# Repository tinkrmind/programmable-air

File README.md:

## NOTE: Development of Programmable-Air has moved to [Programmable-Air Org repo](https://github.com/programmable-air). This repo is maintained for the sake of completeness but is no longer actively maintained. Please use [Programmable-Air Org repo](https://github.com/programmable-air) for code and reference material.

## Buzz

* [Hackaday mention!](https://hackaday.com/2018/05/24/programmable-air-makes-robotics-a-breeze/)
* [Hackster mention!!](https://blog.hackster.io/programmable-air-is-an-arduino-based-air-pump-for-your-soft-robotics-projects-9945c6ed96aa)
* [Maker Faire](https://makerfaire.com/maker/entry/67747/)

## Elevator Pitch

### [Slideshow](https://docs.google.com/presentation/d/1pUnGk4v_wuCpisjBpNWZSJUyDwAFb4v1xceV4rX-Uv4/edit?usp=sharing)

I started out making in earnest at IISc where I saw researchers being exploited by hardware manufacturers. Sub-par equipment is often lauded as the best solution only because it's the only solution. As a result I worked directly with researchers making equipment for measuring elephant height, insect wing- beat frequency, underwater gates for fishes.. I see the same issue with soft robotics today.

The field of inflatable robotics is still in its infancy. So there are a lot of low hanging fruit up for grabs. As such, the more people involved in active experimentation, the faster the field will mature.

Working with inflatables involves a lot of prototyping as a part of the design process. To do any repeatable experiments with inflatables, a controllable air source is required.

I feel there isn't any affordable and easy to use programmable air source available for makers right now. This is a barrier to entry. Programmable Air is my attempt to create a bottom of the line air source that is cheaper and easier to use than anything available right now. The market is strapped for cash makers and schools.

### What can you use it for?

#### Vacuum

###### [* Electronic component pick and place.](https://vimeo.com/268358924)

###### [* Universal vacuum based gripper.](https://vimeo.com/268358891)

#### Inflatable

###### [* Crazy soft robots]()

###### [* Balloons!](https://vimeo.com/268358970)

##### [* Small air brush?](https://vimeo.com/268163619)

Doesn't really work. You can get it to work if the air brush is pointing down and mars is on retrograde :P Check out the failed video below. Maybe it'll give you an idea for how you can improve on it.

 Most airbrushes seem to require around 10L/min air flow rate and the current pump can only deliver 1-2L/min. This small one just barely works with the pumps.

#### Pressure sensor

##### [* Large Impact Sensors]((https://vimeo.com/268358944)

Any closed inflated object can be used as an impact sensor when connected to the air pressure sensor e.g. a large flexible tube with one end closed off and another connected to the pressure sensor. When the tube is pressed a pressure spike is recorded by the sensor. This tube can be looped around a bumper car for example to act as an impact sensor.

##### [Exhalation](https://vimeo.com/268359027)

Controlling the air pressure inside a closed chamber allows a soft robot place in the chamber to behave as if it is being controlled without any tubes connected to  it. This facilitates easy prototyping and some funky art pieces. Inspired from [Exhalation](http://escapepod.org/2009/04/10/ep194-exhalation/) by Ted Chiang.

### What's wrong with the current solutions?

#### Pneuduino: [link](http://pneuduino.org/)

Not available for purchase. Potentially fallen out of development(last commit on github was about two years and the primary engineer has graduated out of the program.)

#### Fluidic control system: [link](https://softroboticstoolkit.com/book/control-board)

Truly designed by researchers for reserchers. Ugly. Complicated to setup. Needlessly expensive. [BOM](https://softroboticstoolkit.com/book/controlboard-bom)

Methods of potentially reducing cost:

- __Cheaper pump__: The [current pump](http://ph.parker.com/us/12051/en/btc-iis-and-ttc-iis-miniature-diaphragm-pump) at ~288$ is overpriced if not necessarily overspec'ed. I'm confident a replacement would be available for one tenth the cost.
- __Cheaper valves__: High switching rate is not necessary for most applications. The current valves cost ~175$. An acceptable replacement would be [this](https://www.elecrow.com/dc12v-four-way-valve-independent-control-solenoid-valve.html) at ~10$. Since pressure is controlled by PWM of the valves, this may lead to some issues if these actuators can't be driven fast enough. Some slack can be made up for by adding a "capacitor" after the valve. But, if the actuation time is of the order of hundreds of milliseconds, I may need a different approach. One such approach can be servo driven drip knobs. Another approach could be a linear actuator driving a plate covering a slit
- __Get rid of the power boards__: There's no need for a 24V in which then gets converted to 12V and 5V on board. It adds bulk and points of failure. Separate 12V and 5V wall warts will be much more reliable and cheaper. Cost saving ~20$
- Get rid of mosfets: A ULN2803 would be just as well suited to the task at a fraction of the price. It would also be much more reliable against electrostatic shock.
- __Cheaper air pressure sensors__: The same vendor makes [pressure sensors](https://www.digikey.com/product-detail/en/honeywell-sensing-and-productivity-solutions/NBPLANN100PAUNV/480-5540-ND/3475899) at a forth the price, which only need minimal external circuit to become nearly as accurate. This would add complexity to the first design of the build but bulm manufacture would benefit from the cost saving.
- __Cheaper arduino alternative__: An arduino mega is overkill for this. Any atmega324 based boards is sufficient

The __weakest link__ in this setup however is the __mess of jumper cable__ connections. There is no justifiable reason for a beginners kit to be this complicated to setup especially when the cost can be reduced simultaneously by making the setup into a PCB.

### Let's start making!

The common pressures are of the range -0.5 atm to 2.5 atm. Ideally we'd want to work in this entire range. Ideally, the pressure profile would be editable over a web interface, without any software/driver installation.

#### Learning basic fluid mechanics and the lingo of the field

Choosing a pressure sensor is tough! There's far too many choices and every datasheet seems to have come from a different universe. Who uses hectoPascals?! Here's some bare minimum info you need before searching for sensors:

-  [Difference between absolute, guage and differential sensors](https://www.first-sensor.com/en/products/pressure-sensors/pressure-sensors-and-transmitters/pressure-types.html)
- [DigiKey sensor guide](https://www.digikey.com/en/resources/sensors/pressure-sensors)
- [Basic of fluid physics](http://www.pneumaticsonline.com/BasicTraining/default.htm)

### Minimum Viable Product

The problem to be solved here is reducing cost without compromising on function. To reduce cost, component specifications have to be matched. The max pressure deliverable by the motor should be close to the pressure limits of the sensor. Given dozens of choices for sensors, motors and valves this is not an easy exercise. Especially, when we're aiming at a moving target specification.

To make life easier, I decided to go for following minimum specifications
* -0.5 atm to +0.5 atm pressure range,
* two air channels
* 2 Liter/min flow rate
* Able to inflate and deflate a 6 inch balloon in under 30 seconds
* Five minute setup time
* Cross platform compatability(Win, Mac, Linux)
* Cost under 100$/set for a production run of 5 sets

### Evaluating off the shelf components

|Item|Inner Dia Eqv|Voltage|Link|Cost per item|Remarks|
|---|---|---|---|---|---|
|Similk aquarium +pump|3/16"|6V|[Amazon](https://www.amazon.com/gp/product/B071FC3C9L/ref=ox_sc_act_title_3?smid=A30FBXYHCPC2G9&psc=1)|4$||
|DIminus aquarium +pump|3/16"|6V|[Amazon](https://www.amazon.com/gp/product/B071GNFHGX/ref=ox_sc_act_title_1?smid=A1KXN55BWHRB5I&psc=1)|4.5$||
|Medical -pump|3/16"|12V|[Amazon](https://www.amazon.com/gp/product/B01MR3JZZF/ref=ox_sc_act_title_4?smid=A3BG62S1F23IH5&psc=1)|9$||
|Square Medical -pump|3/16"|12V|[Amazon](https://www.amazon.com/gp/product/B071GNFHGX/ref=ox_sc_act_title_1?smid=A1KXN55BWHRB5I&psc=1)|11$|Low stock|
|Ohaha tube connectors|3/16"|N/A|[Amazon](https://www.amazon.com/gp/product/B06XHX1KWL/ref=ox_sc_act_title_1?smid=A1665Y00LA4JOM&psc=1)|8$/set of hundred connectors||
|Aquarium -pump|3/16"|5-12V|[Amazon](https://www.amazon.com/Electric-Self-Priming-Suction-Aluminum-Diaphragm/dp/B0786CX98Q/ref=pd_day0_199_5?_encoding=UTF8&pd_rd_i=B0786CX98Q&pd_rd_r=Y0RNFT06BCCAAB1NR6KJ&pd_rd_w=0L70O&pd_rd_wg=gJkuo&psc=1&refRID=Y0RNFT06BCCAAB1NR6KJ)|10$||
|Pink-day -pump|3/16"|12V|[Amazon](https://www.amazon.com/Pink-day-Electric-Motor-Vacuum-Booster/dp/B076VLXHYB/ref=sr_1_9?ie=UTF8&qid=1523048670&sr=8-9&keywords=vacuum+pump+mini)|5$|Slow shipping|
|Woolf -pump|3/16"|3-6V|[Amazon](https://www.amazon.com/3V-6V-Motor-Vacuum-Aquarium-Oxygen/dp/B074PPV6QH/ref=sr_1_15?ie=UTF8&qid=1523048670&sr=8-15&keywords=vacuum+pump+mini)|4$|Slow Shipping|
|Valve 2way|3mm|5V|[Amazon](https://www.amazon.com/gp/product/B00JR3ZQSC/ref=od_aui_detailpages00?ie=UTF8&psc=1)|7.5$||
|Omron +-pressure sensor|3mm|Wheatstone|[DigiKey](https://www.digikey.com/product-detail/en/omron-electronics-inc-emc-div/2SMPP03/Z3639-ND/3671590)|8$|Needs HX711+LM10CN or [INA125](https://learn.adafruit.com/smart-cocktail-shaker/hardware) to work with arduino|
|3 way valve|3/16"|12V|[Elecrow](https://www.elecrow.com/electric-2-position-3-way-12v-micro-solenoid-valve-for-gas.html)|2.5$||
|2 way valve|3/16"|12V|[MPJA](http://www.mpja.com/Solenoid-Valve-Normally-Closed-12VDC-Used/productinfo/33957+HD), [Manufacturer](https://translate.google.com/translate?hl=en&sl=zh-CN&u=http://www.conjoin.com.cn/products.php%3Fl%3D5&prev=search), [SkyCraft](https://www.skycraftsurplus.com/12vdcpneumaticsolenoidvalve-1.aspx)|2.95$|Reused components. Not scalable.|
|2 way valve |3/16"|12V|[Alibaba](https://jmakervalve.en.alibaba.com/product/60692195756-805059697/JMKV20_BB12A1_2_way_12v_dc_water_solenoid_valve_for_high_end_medical_equipment.html?spm=a2700.icbuShop.prewdfa4cf.86.41256ab8Fp0fQF)|

### Choice of pressure sensor: [2SMPP03](https://www.digikey.com/product-detail/en/omron-electronics-inc-emc-div/2SMPP03/Z3639-ND/3671590)

It's easy for the pressure sensor to be the most expensive piece in the kit. Since one pressure sensor is required for every pneumatic channel, the cost scales linearly with number of channels. Pressure sensors that work in <-0.5 atm to >+0.5 atm range are relatively expensive since few large industries demand such a sensor. The cheapest such sensor I could find is [2SMPP03](https://www.digikey.com/product-detail/en/omron-electronics-inc-emc-div/2SMPP03/Z3639-ND/3671590) by Omron electronics. It is priced at <7$/per unit for 5 units and while it needs additional circuitry to work, the effort is well worth it. The cheapest sensor that works standalone is at least 30$/per unit at 5 units. So I have designed the rest of the system around this sensor.

### v0.1 PCB design

Used Aiyima pumps and an Arduino Nano on master board. The slave board has pressure sensor and three two way valves. Upto four slave boards can attach to a single master board, as shown in mock-up below.

#### Learnings from design and manufacture:

The rated current for DC motors can differ highly from the actual current consumed. While the motors are rated at 350mA, a 0.8A transistor blew up while trying to supply enough current to it. This could be because of high stall/startup current. v0.11 will have TIP120 or FET rated to at least 2A. The valves are rated at 0.11A so, using a 2222 transistor seems like a safe bet because they can handle peak currents of up to 0.8A(a 7x margin). Because these are much cheaper than TIP120, it makes sense to use them.

As a result of design oversight, the was no 5V power connection from master to slave board. While 12V input to slave board can be converted to a clean 5V with a relatively cheap regulator, v0.11 will have power connections for 5V as well. Added filter capacitors to all power rails in v0.11.

I manufactured the PCBs in an OtherMill CNC. It is the fastest way I have found to do small run prototypes. Designing for OtherMill manufacture is a completely different game than designing for production from a PCB fab house. Particularly, OtherMill PCBs are constrained to maximum two layers and vias are not plated. Also the tolerances have to be relaxed to allow for easier production. All in all this means you have to be a lot smarter, using minimum number of vias and distributing your components further out.

### Project Update: April 28th

I was finally able to fix the issue with the pressure sensor. I'm using a LM10CN precision opAmp to supply 100uA to the 2SMPP-03 pressure sensor. This results in a 40mV span voltage through the Wheatstone bridge in the sensor, which is read through the HX711 24 bit ADC. While HX711 has the ability to excite the sensor directly, I have not been successful in using this because the IC is poorly documented. LM10CN adds 2.5$ to each pressure sensor unit and complicates the circuit, but the cost savings are still worth the hassle.

I'm looking into using an instrumentation amplifier like INA125 instead of LM10CN+HX711. The cheapest instrumentation amp I could find is 7$, a hefty 3$ more than the HX711+LM10CN setup. Multiply by three/four sensors per kit and that's 10$. not sure if math makes sense. Note that the resolution of data gathered does not matter for this decision(an instrumentation amp would use the Arduino's 10bit ADC vs the 24 bit ADC on HX711), because the data will be corrupted with enough noise that anything above 8 bit resolution should not matter.

I also decided to redesign the boards to be less than 100x50mm in size so that they can be easily manufactured in small batch runs from PCB manufacturers. 100x100mm panel size seems to be a universal cutoff for price variation(at least when it comes to hobby type boards). I utilized this avenue to add M3 mounting holes and standardize the berg stick connectors better.

After using the board for a bit, I realized that most applications call for less than three air channels and I was using the fourth channel almost exclusively for IO. So I put two buttons and a few neopixels on the master board using up the pins from the fourth channel. Now the slave boards can only dock to the bottom or sides of the master boards, and not to the top. The top has easily accessible power connection, USB, buttons and neopixels. I also added LEDs to indicate the state of the pumps and valves. And I put the pumps on analogWrite pins for the atmega328. This will allow me to easily control the pumping speed.

As an additional fun challenge, I decided to only use curved angles in the PCB traces. I think the PCBs came out looking rather sharp. On the practical side, since I manufacture PCBs with a CNC the lack of sharp corners translates to quieter, less jerky operation while manufacturing.

### Working with Balloons - Case for flow meter

Programmable Air gets feedback from a pressure sensor. This is because I was following an unwritten intuition that the pressure inside an inflatable is proportional to the volume of air pumped in. Boy! is that intuition wrong! For rubber inflatables like latex balloons or thin walled silicone the pressure initially increases with the air flow but then starts decreasing. The balloon is more of a flow driven device than a pressure driven device. To control something like this a flow meter makes much more sense. The initial case against a flow meter was because of leaks. It makes sense to have a flow sensor to use in conjunction with a pressure sensor as well. I'm on the lookout for a cheap flow sensor.

**Result**: Flow sensors are too expensive! Like 80$ for a [cheap one](https://www.digikey.com/product-detail/en/honeywell-sensing-and-productivity-solutions/AWM1100V/AWM1100V-ND/2552655). Not even gonna think about using it for a while.

### Changes I'd like to work on:
* LittleBits or mCookie like magnetic snap connectors instead of dupont sticks. Failing that, just plain better connections.. dupont connectors aren't meant for this kind of mechanical strains. Maybe old school RS232 or serial type stuff?
* Manage power to motors and solenoids better. e.g. Arduino USB should not power the motors when no Vin is provided.
* Make pneumatic connections via simple snapping as well. Individually connecting cables is so 2000's :P
* Simpler custom connectors to make pneumatic connections. Aquarium type connectors are very restrictive.
* Cheap 3mm to 3/16th converter

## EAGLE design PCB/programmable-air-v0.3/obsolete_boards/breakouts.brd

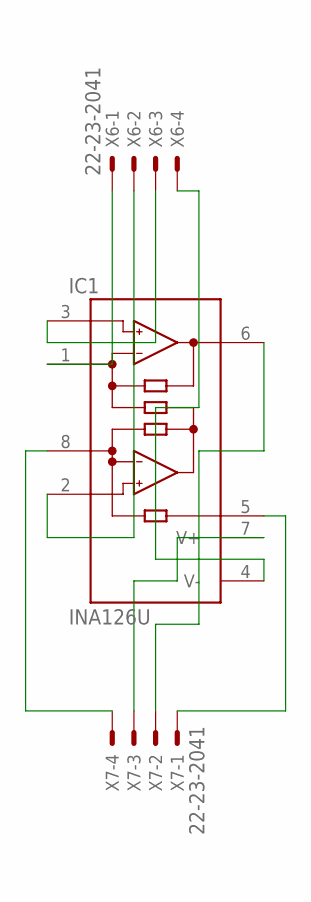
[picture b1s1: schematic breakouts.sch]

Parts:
IC1: INA126U; SO08
X6, X7: 22-23-2041

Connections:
unnamed: IC1.1 (RG), X6.1
unnamed: IC1.2 (-IN), X6.2
unnamed: IC1.3 (+IN), X6.3
unnamed: IC1.4 (V-), X6.4
unnamed: IC1.5 (REF), X7.1
unnamed: IC1.6 (OUT), X7.2
unnamed: IC1.7 (V+), X7.3
unnamed: IC1.8 (RG), X7.4

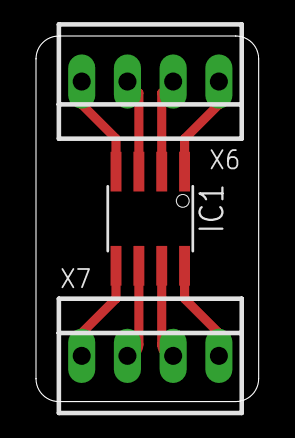
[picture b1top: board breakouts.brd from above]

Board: 2 copper layers, 12.4 x 20.3 mm, 3 parts (0 on the bottom side), 8 nets.

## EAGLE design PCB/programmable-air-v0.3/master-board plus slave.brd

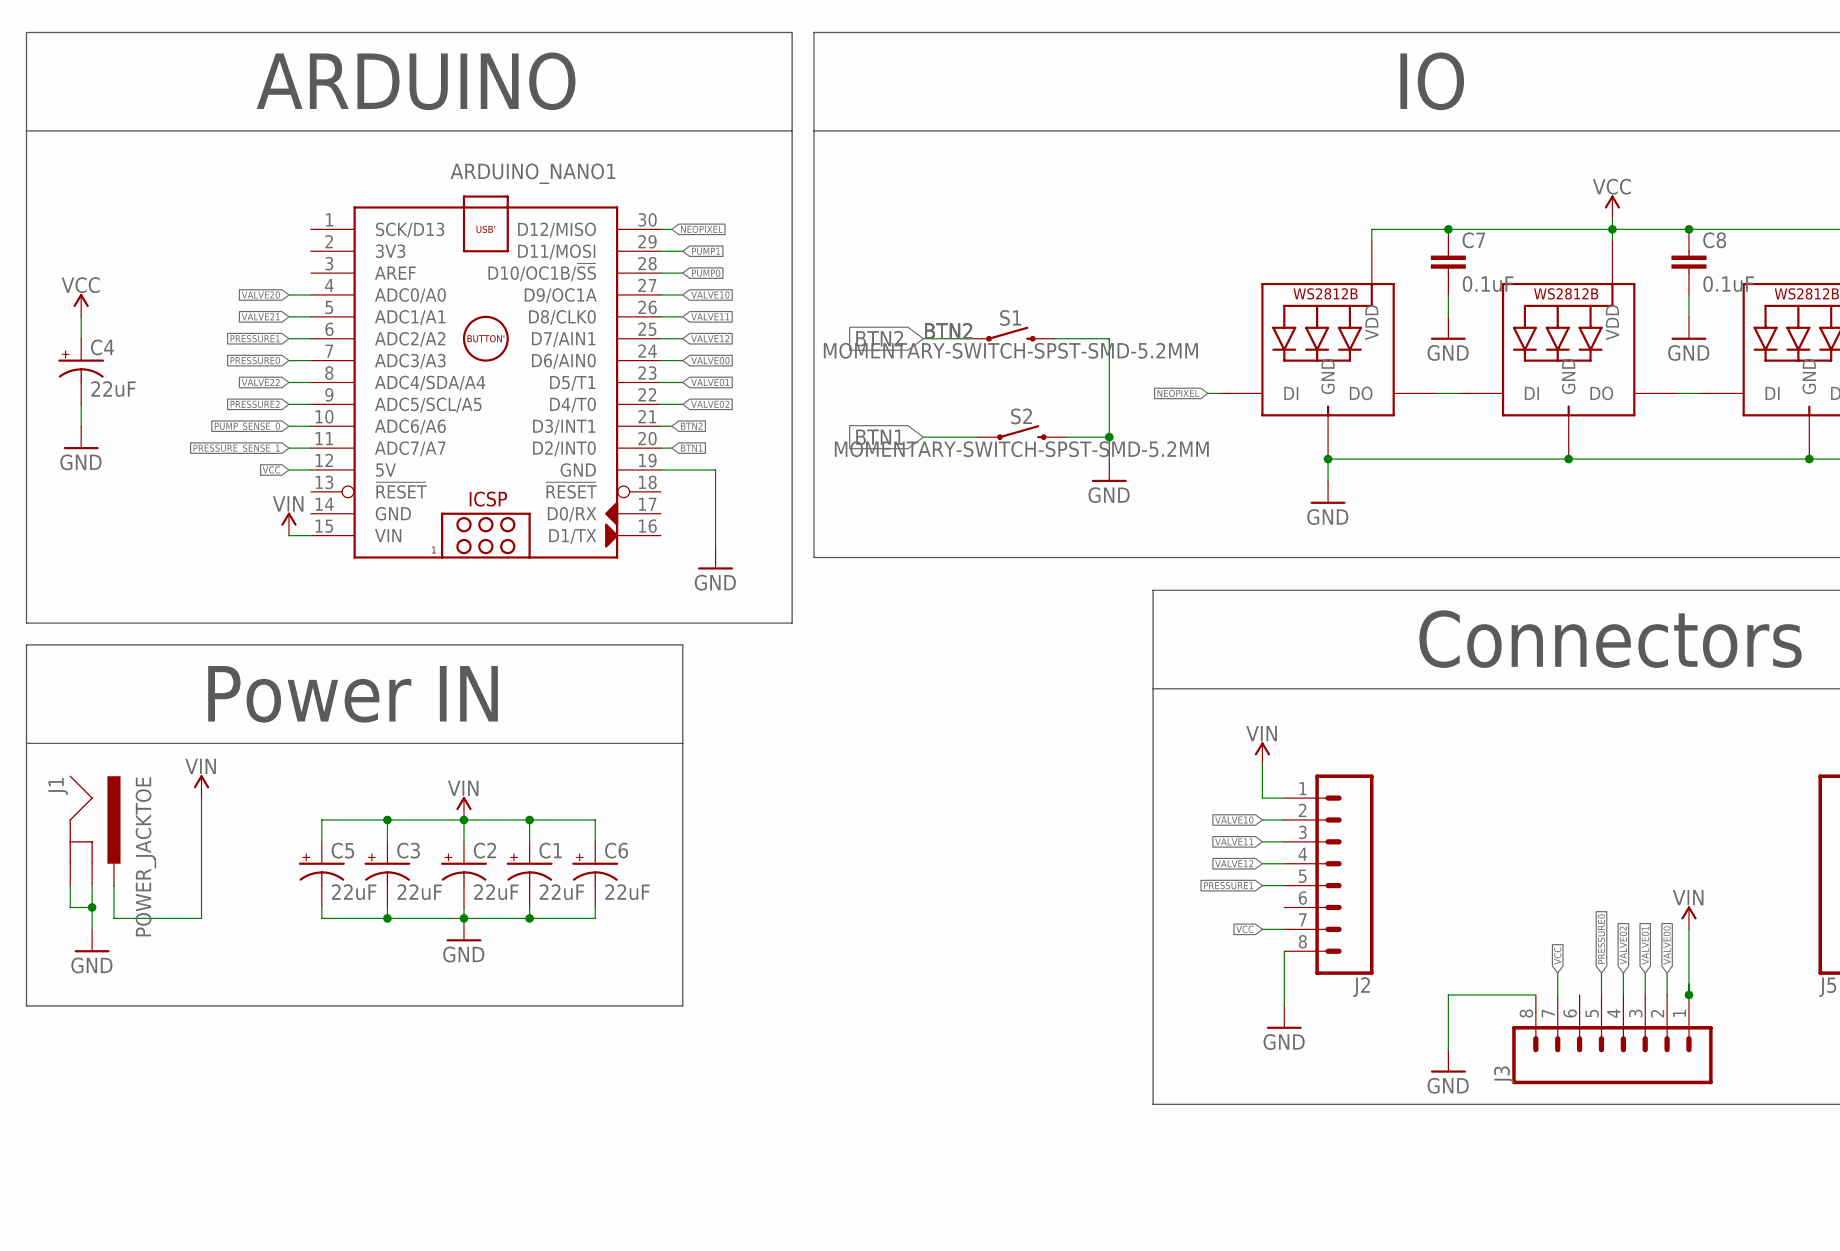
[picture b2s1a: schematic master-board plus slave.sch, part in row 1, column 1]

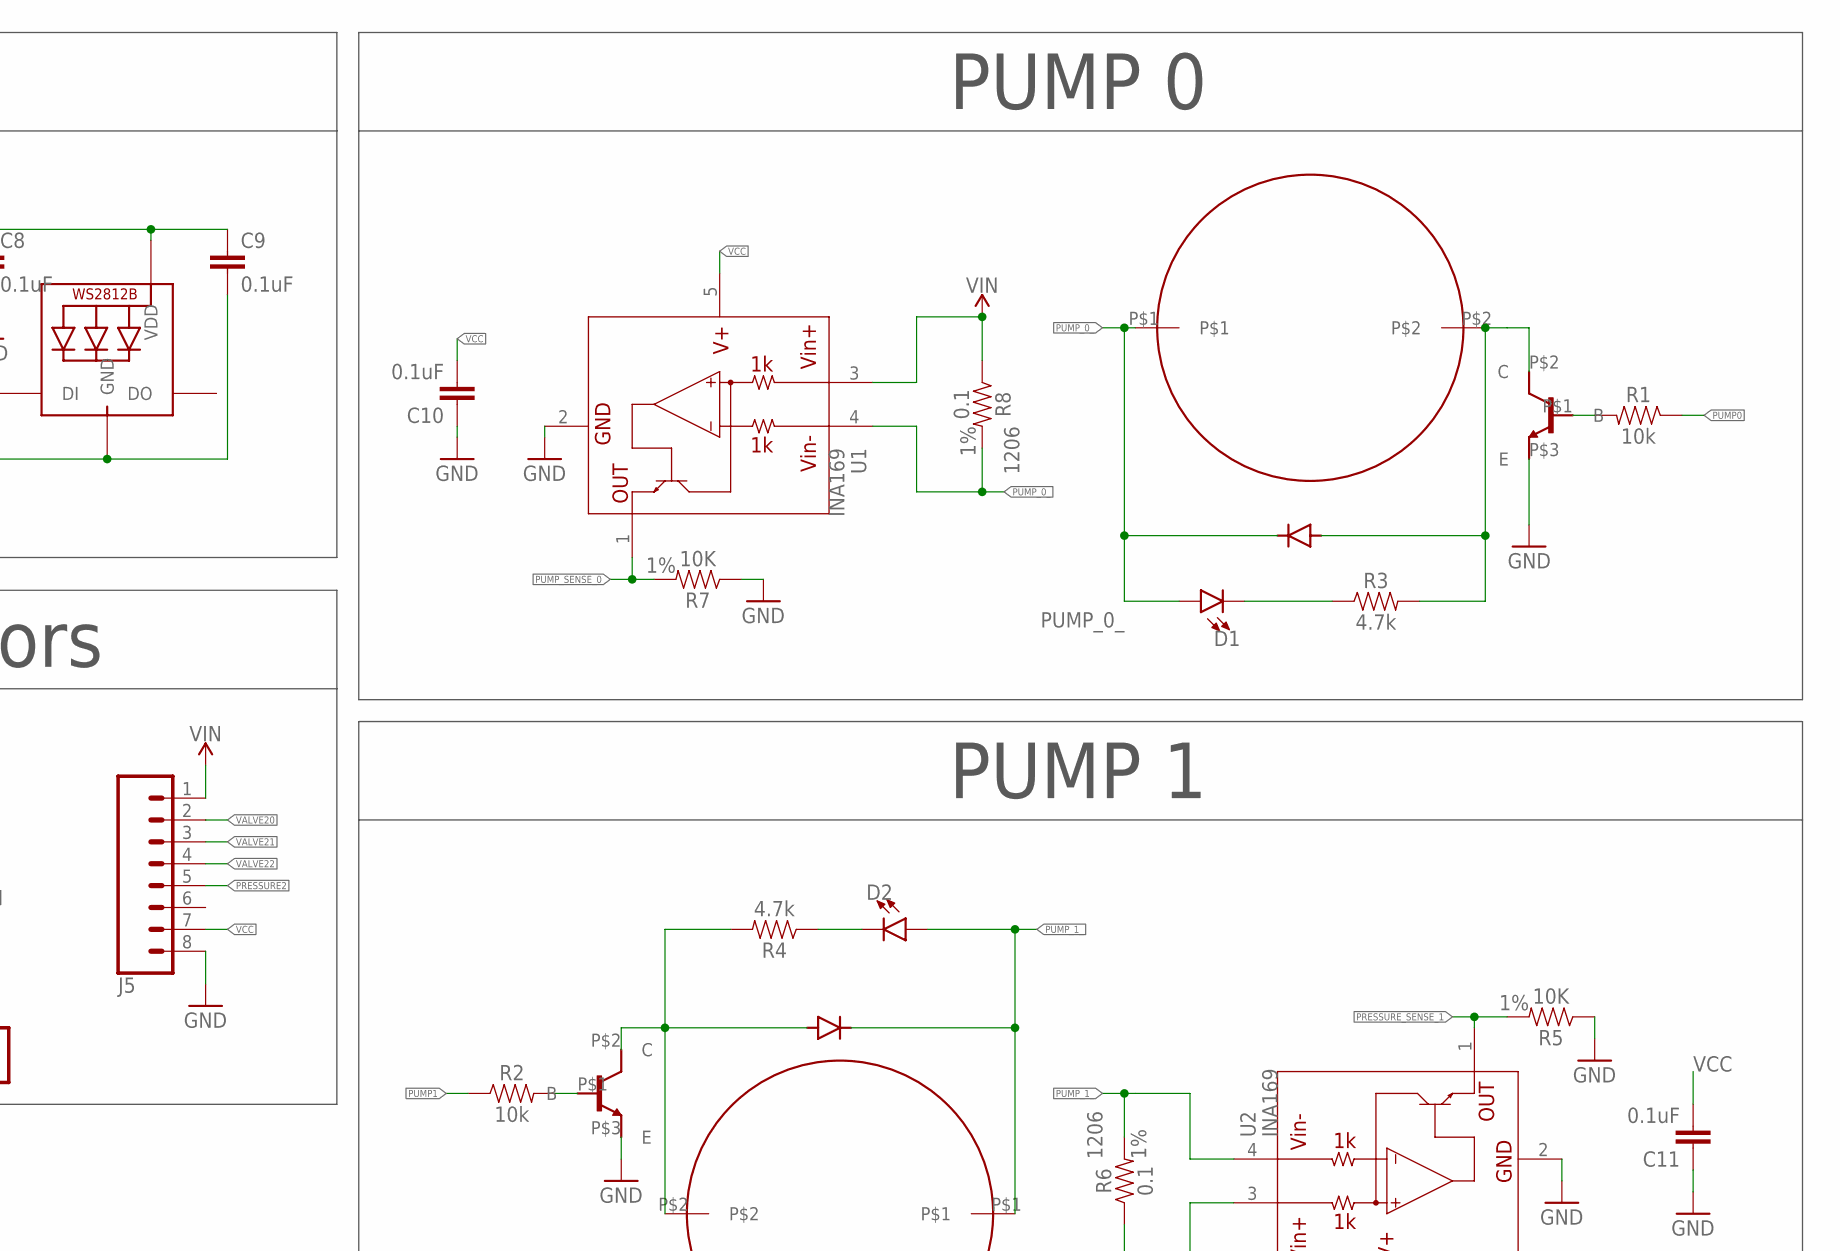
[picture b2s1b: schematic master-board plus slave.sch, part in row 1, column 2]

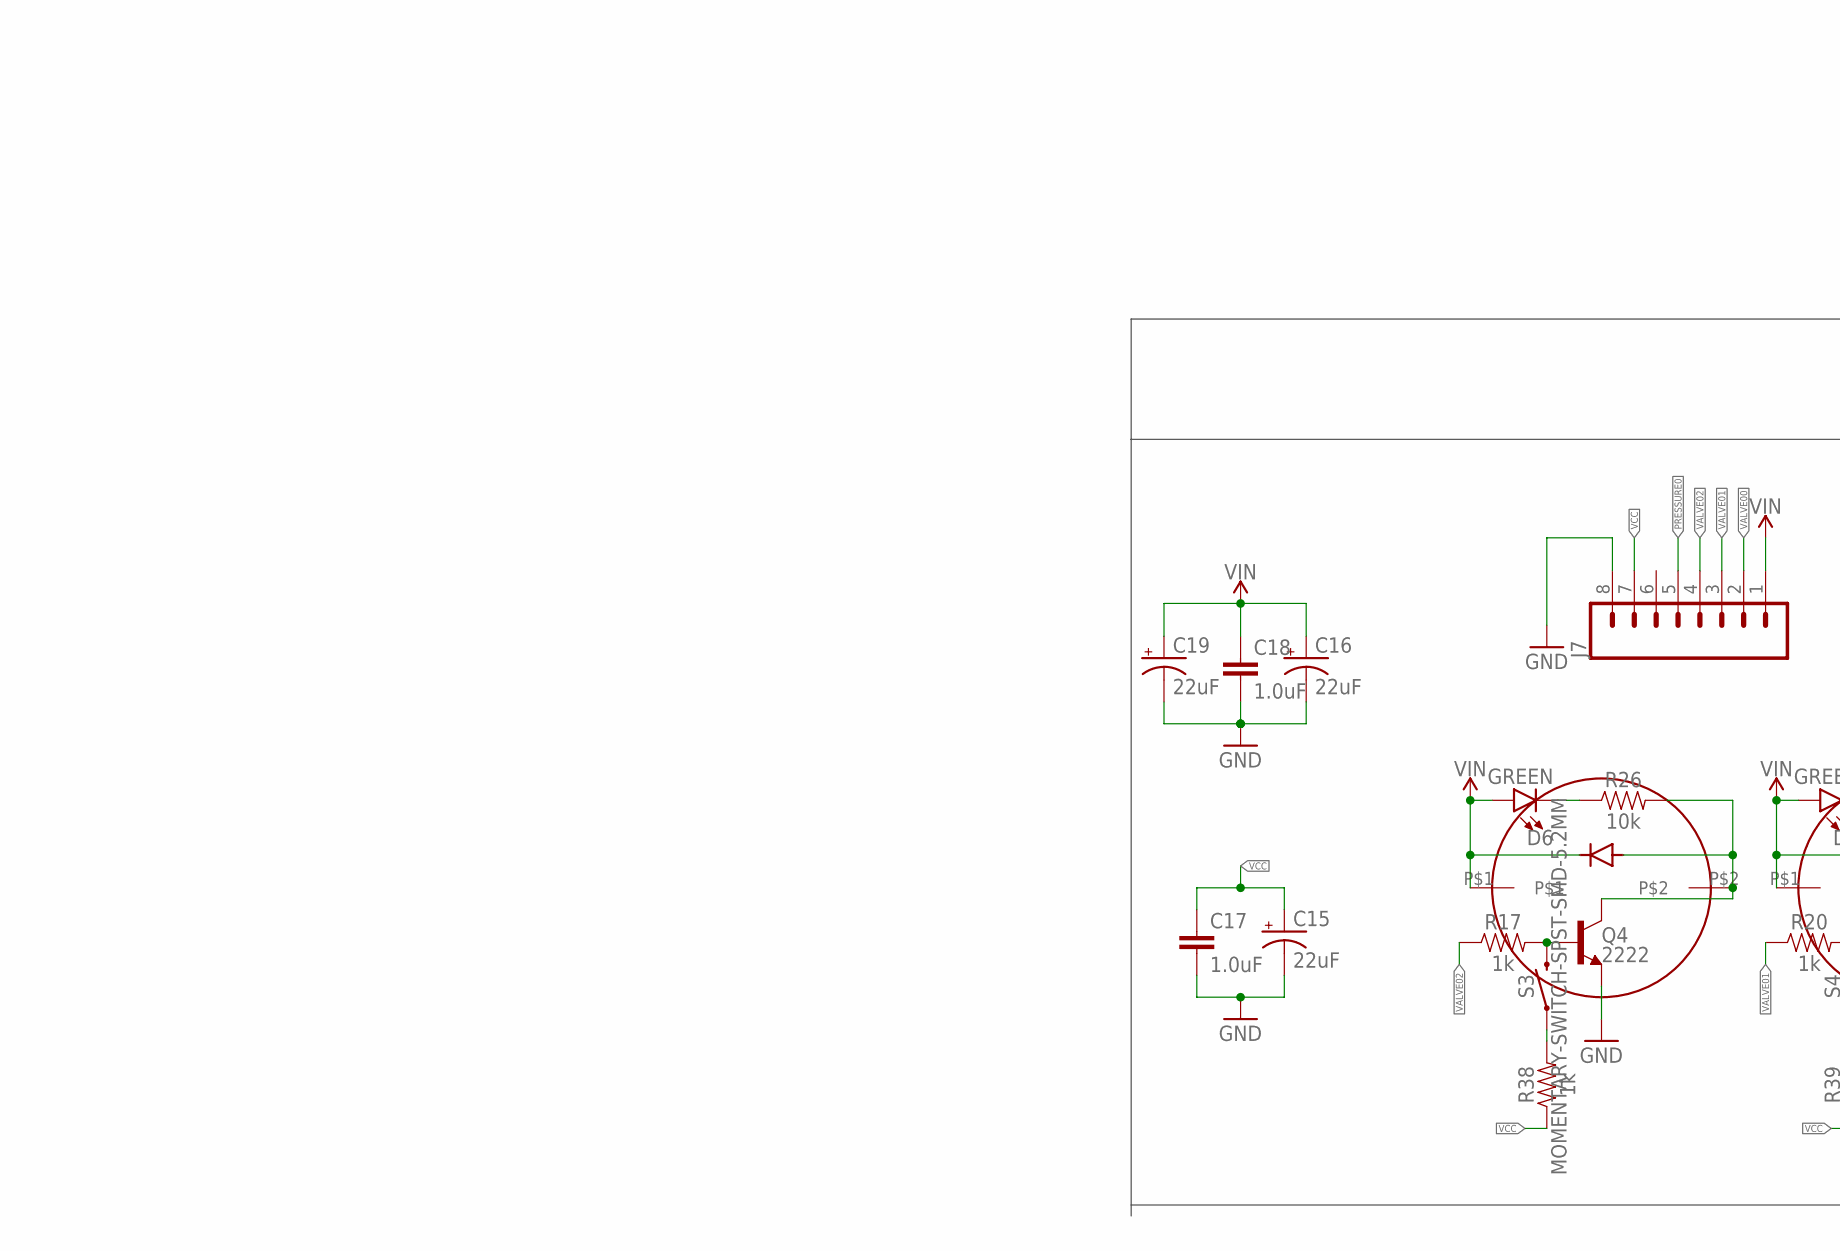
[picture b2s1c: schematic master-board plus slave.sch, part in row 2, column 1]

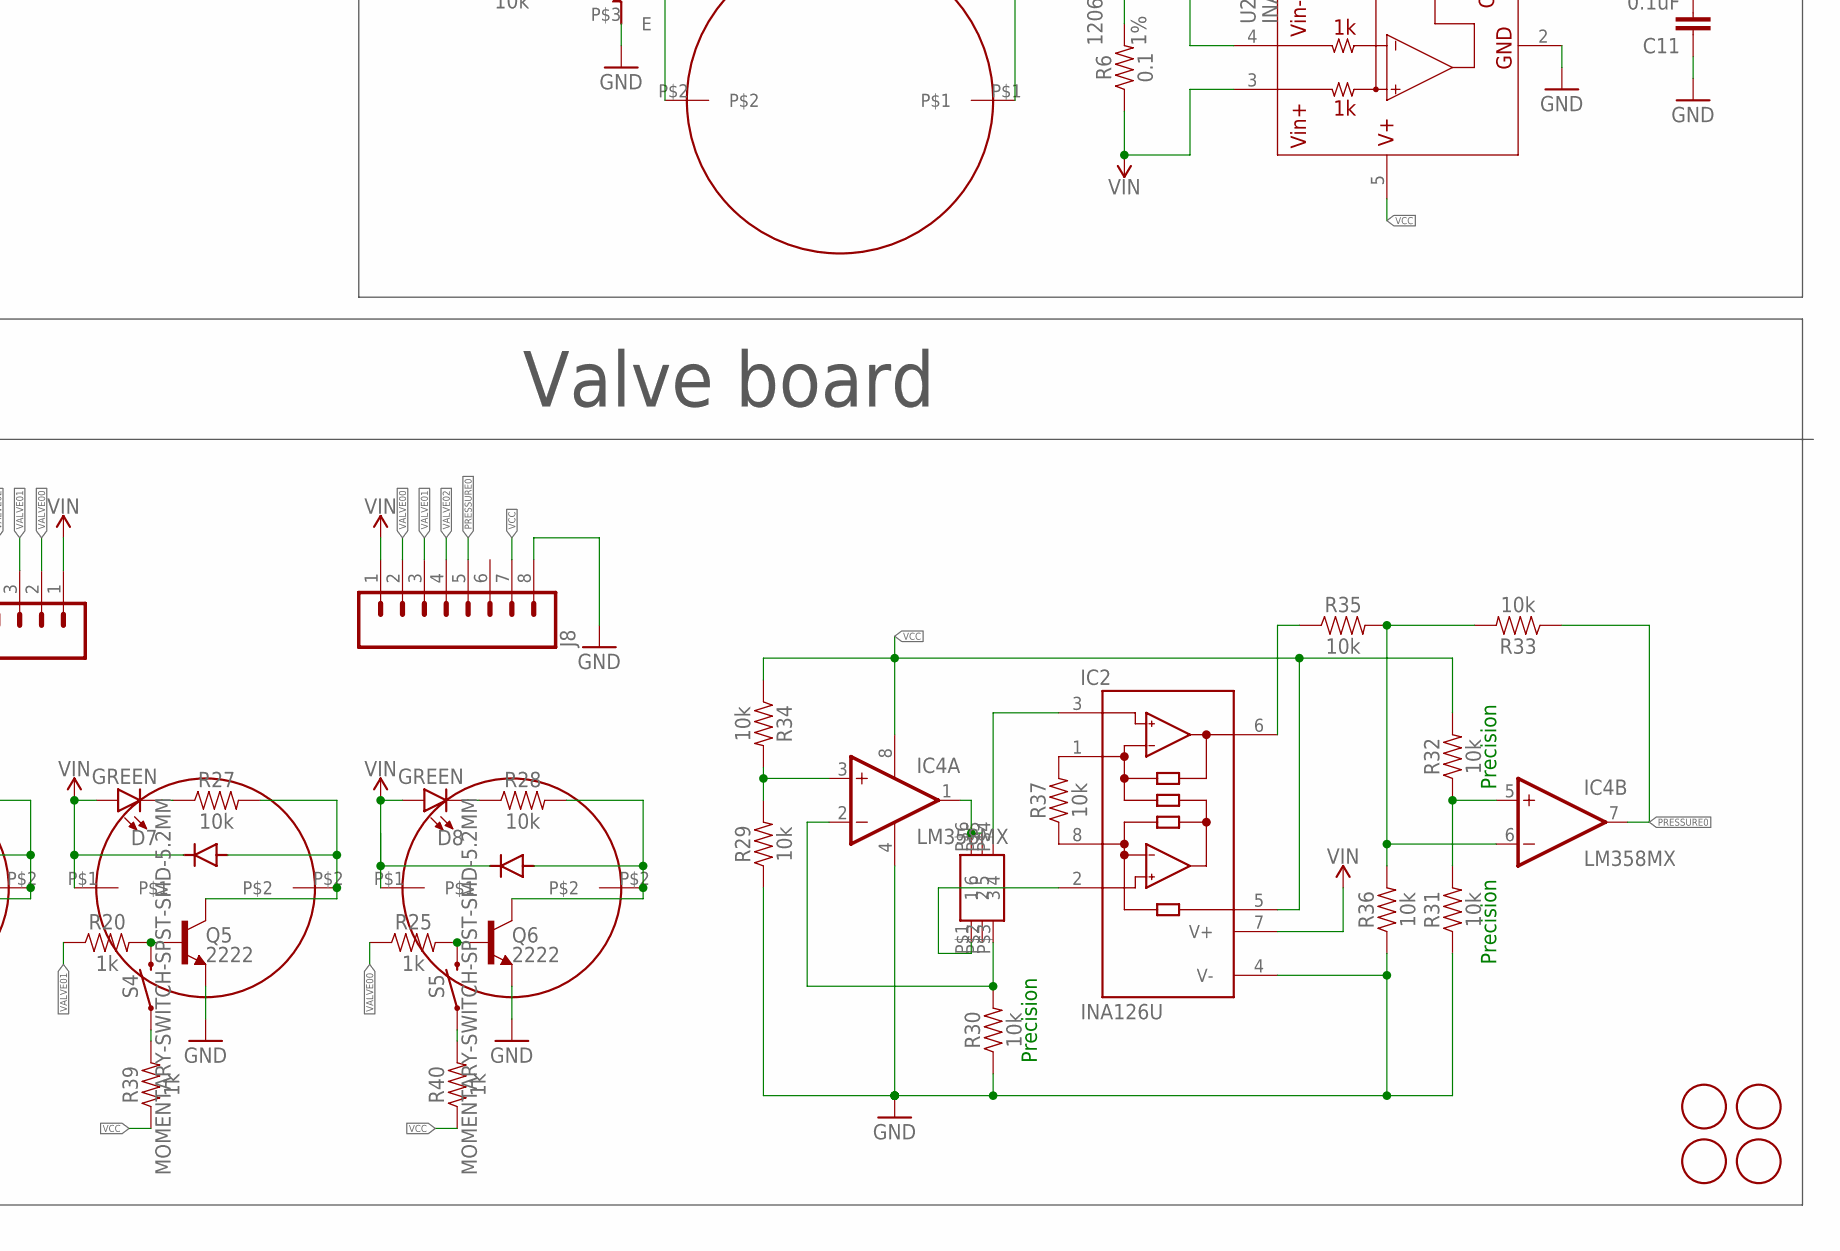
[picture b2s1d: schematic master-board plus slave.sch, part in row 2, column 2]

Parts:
ARDUINO_NANO1: ARDUINO_NANO
C1, C2, C3, C4, C5, C6, C15, C16, C19: 22uF; PANASONIC_C
C7, C8, C9: 0.1uF; 0603
C10, C11: 0.1uF; 0603-CAP
C17, C18: 1.0uF; 0603
D1, D2: LED0603; LED-0603
D6, D7, D8: GREEN; LED-0603
IC2: INA126U; SO08
IC4: LM358MX; SO08
J1: POWER_JACKTOE; POWER_JACK_SMD_OVERPASTE_TOE
J2: CONN_08FLIPPED; 1X08
J3: CONN_08"; 1X08
J5: CONN_081X08_FEMALE_FLIPPED; 1X08_FEMALE_FLIPPED
J7: CONN_08; 1X08_MALE_FLIPPED
J8: CONN_08NO_SILK_FEMALE_PTH; 1X08_NO_SILK
LED1, LED2, LED3: WS2812B5050; WS2812B
Q4, Q5, Q6: 2222; SOT23-3
R1, R2, R26, R27, R28, R29, R30, R31, R32, R33, R34, R35, R36, R37: 10k; 0603
R3, R4: 4.7k; 0603
R5, R7: 10K; 0603
R6, R8: 0.1; 1206
R17, R20, R25, R38, R39, R40: 1k; 0603
S1, S2, S3, S4, S5: MOMENTARY-SWITCH-SPST-SMD-5.2MM; TACTILE_SWITCH_SMD_5.2MM
U1, U2: INA169; SOT23-5
U$1, U$2: AIYIMA-PUMP-A5F083; A5F083
U$3, U$4, U$20, U$21, U$22: IN4148
U$5, U$6: TIP120-TO220; TO220
U$9, U$10, U$11, U$12: FIDUCIAL; FIDUCIAL_1MM
U$17, U$18, U$19: CJV23-SOLENOID-VALVE; CJV23
U$23: 2SMPP-03

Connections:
BTN1: ARDUINO_NANO1.20 (D2/INT0), S2.1
BTN2: ARDUINO_NANO1.21 (D3/INT1), S1.1
GND: ARDUINO_NANO1.14 (GND), ARDUINO_NANO1.19 (GND), C1.-, C2.-, C3.-, C4.-, C5.-, C6.-, C7.2, C8.2, C9.2, C10.1, C11.1, C15.-, C16.-, C17.2, C18.2, C19.-, IC2.4 (V-), IC4.4 (V-), J1.GND (GNDBREAK), J1.P$4 (GND), J2.8, J3.8, J5.8, J7.8, J8.8, LED1.3-GND (GND), LED2.3-GND (GND), LED3.3-GND (GND), Q4.2 (E), Q5.2 (E), Q6.2 (E), R5.1, R7.1, R29.1, R30.1, R31.1, R36.1, S1.3 (2), S2.3 (2), U1.2 (GND), U2.2 (GND), U$5.P$3 (E), U$6.P$3 (E)
unnamed: R1.2, U$6.P$1 (B)
unnamed: R3.2, U$1.P$2, U$3.P$2, U$6.P$2 (C)
unnamed: R4.2, U$2.P$2, U$4.P$2, U$5.P$2 (C)
unnamed: R2.2, U$5.P$1 (B)
unnamed: D1.C, R3.1
unnamed: D2.C, R4.1
unnamed: LED2.2-DOUT (DO), LED3.4-DIN (DI)
unnamed: LED1.2-DOUT (DO), LED2.4-DIN (DI)
unnamed: Q4.1 (B), R17.2, S3.3 (2)
unnamed: Q5.1 (B), R20.2, S4.3 (2)
unnamed: Q6.1 (B), R25.2, S5.3 (2)
unnamed: Q6.3 (C), R28.2, U$19.P$2, U$22.P$2
unnamed: Q5.3 (C), R27.2, U$18.P$2, U$21.P$2
unnamed: Q4.3 (C), R26.2, U$17.P$2, U$20.P$2
unnamed: D8.C, R28.1
unnamed: D7.C, R27.1
unnamed: D6.C, R26.1
unnamed: IC2.2 (-IN), U$23.P$1 (1)
unnamed: IC4.1 (OUT), U$23.P$5 (5), U$23.P$6 (6)
unnamed: IC2.3 (+IN), U$23.P$4 (4)
unnamed: IC4.3 (+IN), R29.2, R34.2
unnamed: IC2.8 (RG), R37.1
unnamed: IC2.1 (RG), R37.2
unnamed: IC4.6 (-IN), R33.2, R35.2, R36.2
unnamed: IC4.5 (+IN), R31.2, R32.1
unnamed: IC4.2 (-IN), R30.2, U$23.P$3 (3)
unnamed: IC2.6 (OUT), R35.1
unnamed: R38.2, S3.1
unnamed: R39.2, S4.1
unnamed: R40.2, S5.1
NEOPIXEL: ARDUINO_NANO1.30 (D12/MISO), LED1.4-DIN (DI)
PRESSURE0: ARDUINO_NANO1.7 (ADC3/A3), IC4.7 (OUT), J3.5, J7.5, J8.5, R33.1
PRESSURE1: ARDUINO_NANO1.6 (ADC2/A2), J2.5
PRESSURE2: ARDUINO_NANO1.9 (ADC5/SCL/A5), J5.5
PRESSURE_SENSE_1: ARDUINO_NANO1.11 (ADC7/A7), R5.2, U2.1 (OUT)
PUMP0: ARDUINO_NANO1.28 (D10/OC1B/!SS), R1.1
PUMP1: ARDUINO_NANO1.29 (D11/MOSI), R2.1
PUMP_0_: D1.A, R8.2, U1.4 (VIN-), U$1.P$1, U$3.P$1
PUMP_1_: D2.A, R6.2, U2.4 (VIN-), U$2.P$1, U$4.P$1
PUMP_SENSE_0: ARDUINO_NANO1.10 (ADC6/A6), R7.2, U1.1 (OUT)
VALVE00: ARDUINO_NANO1.24 (D6/AIN0), J3.2, J7.2, J8.2, R25.1
VALVE01: ARDUINO_NANO1.23 (D5/T1), J3.3, J7.3, J8.3, R20.1
VALVE02: ARDUINO_NANO1.22 (D4/T0), J3.4, J7.4, J8.4, R17.1
VALVE10: ARDUINO_NANO1.27 (D9/OC1A), J2.2
VALVE11: ARDUINO_NANO1.26 (D8/CLK0), J2.3
VALVE12: ARDUINO_NANO1.25 (D7/AIN1), J2.4
VALVE20: ARDUINO_NANO1.4 (ADC0/A0), J5.2
VALVE21: ARDUINO_NANO1.5 (ADC1/A1), J5.3
VALVE22: ARDUINO_NANO1.8 (ADC4/SDA/A4), J5.4
VCC: ARDUINO_NANO1.12 (5V), C4.+, C7.1, C8.1, C9.1, C10.2, C11.2, C15.+, C17.1, IC2.5 (REF), IC4.8 (V+), J2.7, J3.7, J5.7, J7.7, J8.7, LED1.1-VDD (VDD), LED2.1-VDD (VDD), LED3.1-VDD (VDD), R32.2, R34.1, R38.1, R39.1, R40.1, U1.5 (V+), U2.5 (V+)
VIN: ARDUINO_NANO1.15 (VIN), C1.+, C2.+, C3.+, C5.+, C6.+, C16.+, C18.1, C19.+, D6.A, D7.A, D8.A, IC2.7 (V+), J1.VIN0 (PWR), J2.1, J3.1, J5.1, J7.1, J8.1, R6.1, R8.1, U1.3 (VIN+), U2.3 (VIN+), U$17.P$1, U$18.P$1, U$19.P$1, U$20.P$1, U$21.P$1, U$22.P$1

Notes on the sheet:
Precision
Power IN
PUMP 0
PUMP 1
ARDUINO
Connectors
Valve board

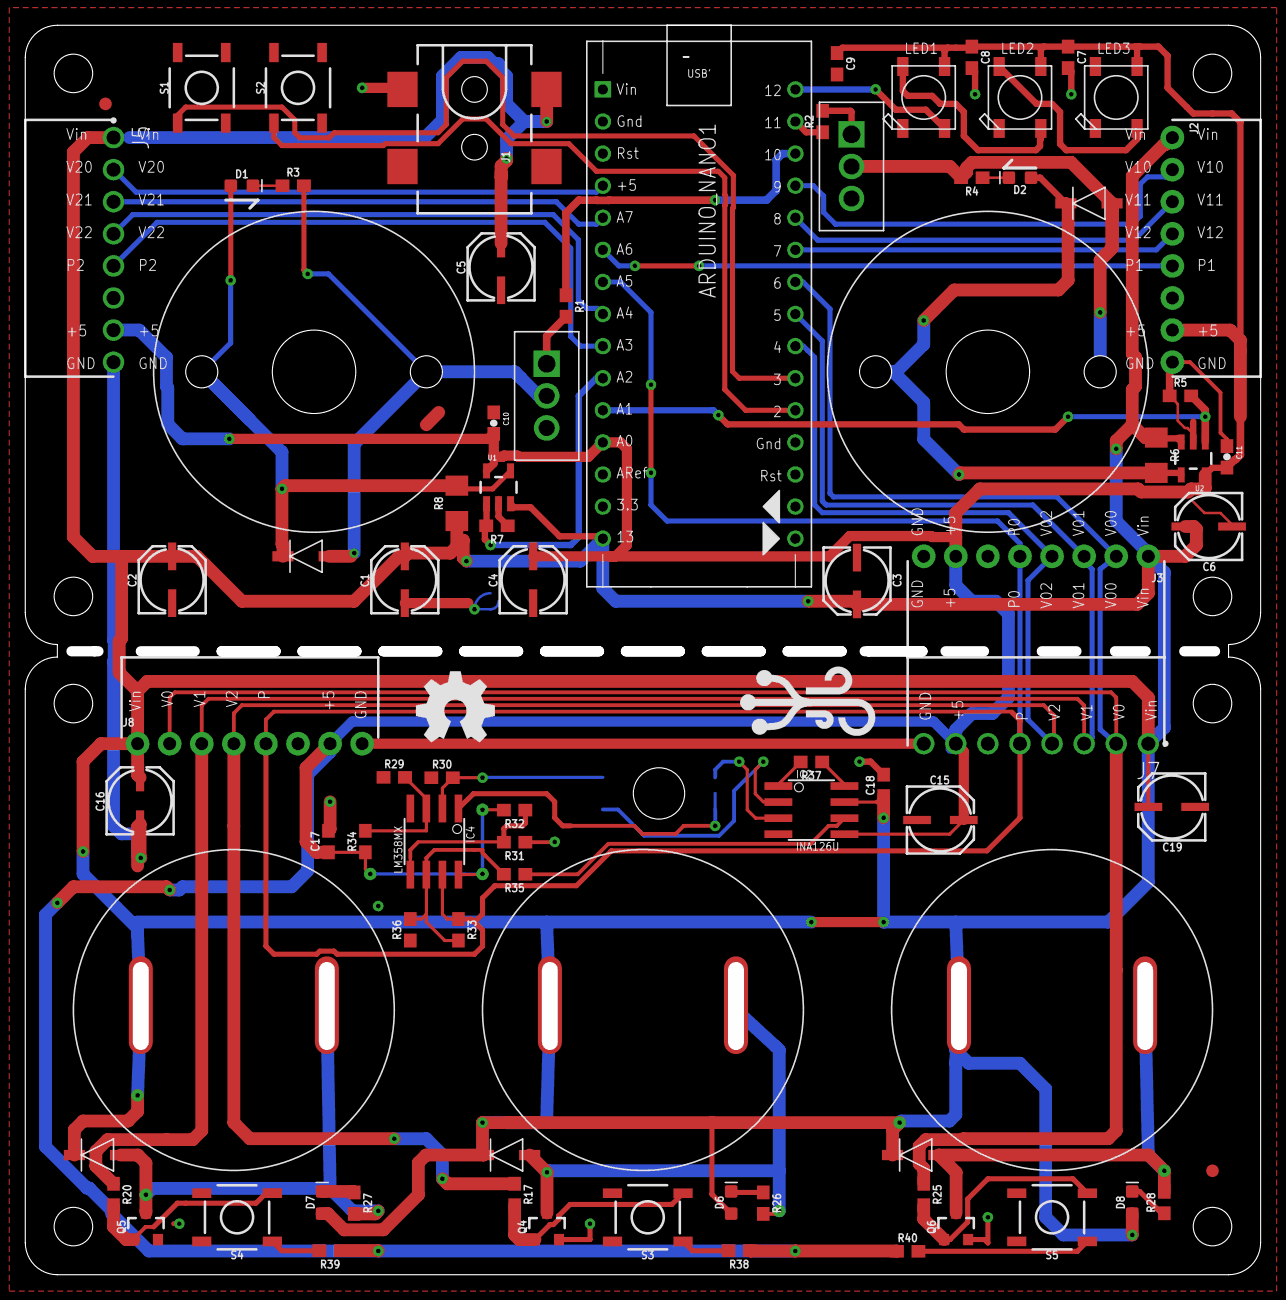
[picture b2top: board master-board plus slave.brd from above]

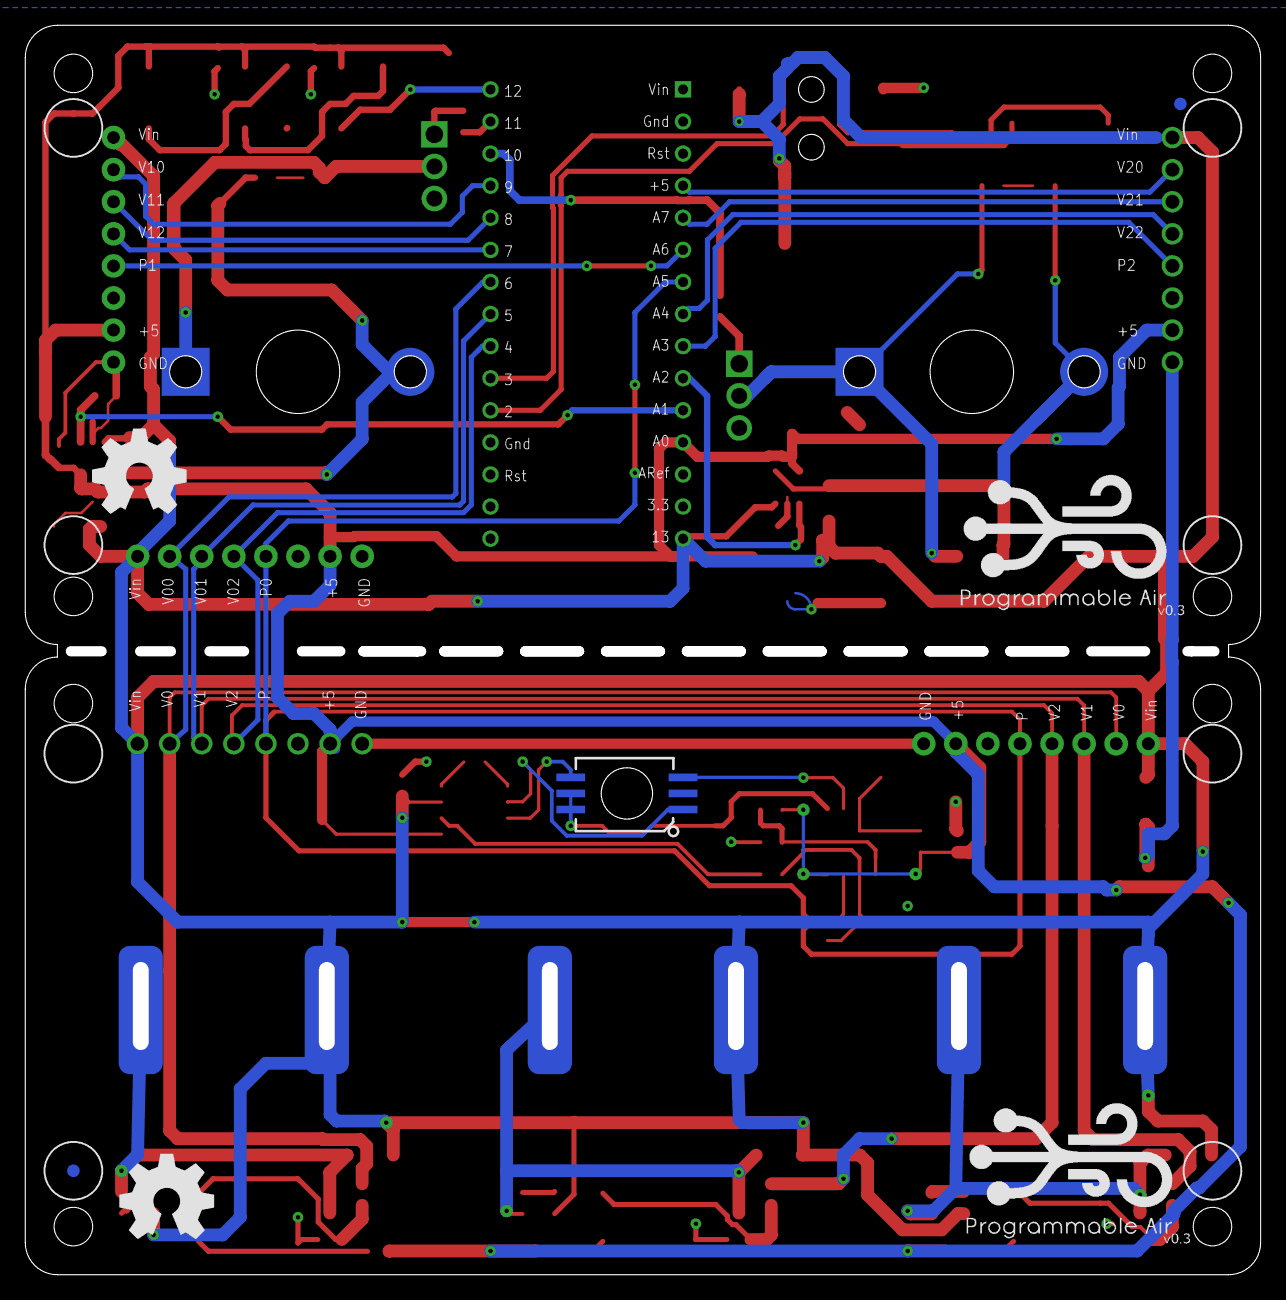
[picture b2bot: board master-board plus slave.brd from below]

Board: 2 copper layers, 97.8 x 98.9 mm, 86 parts (2 on the bottom side), 54 nets.

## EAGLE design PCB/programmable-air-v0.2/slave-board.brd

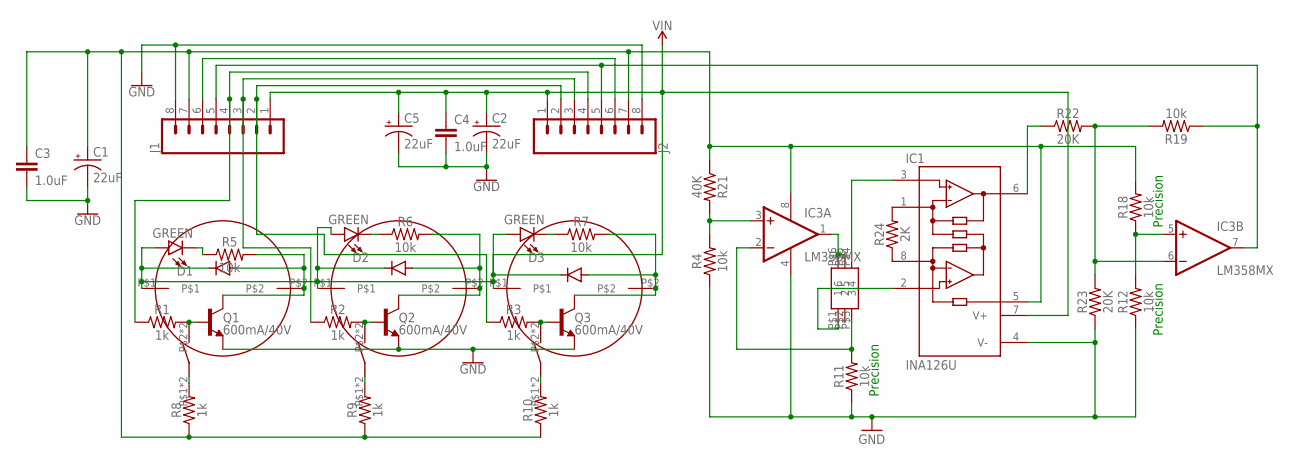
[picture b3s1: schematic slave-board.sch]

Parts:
C1, C2, C5: 22uF; PANASONIC_C
C3, C4: 1.0uF; 0603
D1, D2, D3: GREEN; LED-0603
IC1: INA126U; SO08
IC3: LM358MX; SO08
J1, J2: CONN_08"; 1X08
Q1, Q2, Q3: 600mA/40V; SOT23-3
R1, R2, R3, R8, R9, R10: 1k; 0603
R4, R5, R6, R7, R11, R12, R18, R19: 10k; 0603
R21: 40K; 0603
R22, R23: 20K; 0603
R24: 2K; 0603
U$1: 2SMPP-03
U$2, U$3, U$4: CJV23-SOLENOID-VALVE; CJV23
U$5, U$6, U$7: IN4148
U$8, U$9, U$10: BUTTON

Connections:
GND: C1.-, C2.-, C3.2, C4.2, C5.-, IC1.4 (V-), IC3.4 (V-), J1.8, J2.8, Q1.2 (E), Q2.2 (E), Q3.2 (E), R4.1, R11.1, R12.1, R23.1
unnamed: Q1.1 (B), R1.2, U$8.P$2, U$8.P$4
unnamed: Q2.1 (B), R2.2, U$9.P$2, U$9.P$4
unnamed: Q3.1 (B), R3.2, U$10.P$2, U$10.P$4
unnamed: IC1.2 (-IN), U$1.P$1 (1)
unnamed: J1.2, J2.2, R3.1
unnamed: D3.C, R7.1
unnamed: Q3.3 (C), R7.2, U$4.P$2, U$7.P$2
unnamed: Q2.3 (C), R6.2, U$3.P$2, U$6.P$2
unnamed: Q1.3 (C), R5.2, U$2.P$2, U$5.P$2
unnamed: J1.3, J2.3, R2.1
unnamed: D2.C, R6.1
unnamed: J1.4, J2.4, R1.1
unnamed: IC3.7 (OUT), J1.5, J2.5, R19.1
unnamed: J1.6, J2.6
unnamed: IC1.6 (OUT), R22.1
unnamed: C2.+, C4.1, C5.+, D1.A, D2.A, D3.A, IC1.7 (V+), J1.1, J2.1, U$2.P$1, U$3.P$1, U$4.P$1, U$5.P$1, U$6.P$1, U$7.P$1
unnamed: D1.C, R5.1
unnamed: IC3.1 (OUT), U$1.P$5 (5), U$1.P$6 (6)
unnamed: IC1.3 (+IN), U$1.P$4 (4)
unnamed: R8.2, U$8.P$1, U$8.P$3
unnamed: R9.2, U$9.P$1, U$9.P$3
unnamed: R10.2, U$10.P$1, U$10.P$3
unnamed: IC3.3 (+IN), R4.2, R21.2
unnamed: IC1.8 (RG), R24.1
unnamed: IC1.1 (RG), R24.2
unnamed: IC3.6 (-IN), R19.2, R22.2, R23.2
unnamed: C1.+, C3.1, IC1.5 (REF), IC3.8 (V+), J1.7, J2.7, R8.1, R9.1, R10.1, R18.2, R21.1
unnamed: IC3.5 (+IN), R12.2, R18.1
unnamed: IC3.2 (-IN), R11.2, U$1.P$3 (3)

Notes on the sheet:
Precision

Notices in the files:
parts and their libraries:
SparkFun-Connectors: Licensing: Creative Commons ShareAlike 4.0 International - https://creativecommons.org/licenses/by-sa/4.0
SparkFun-Aesthetics: Licensing: CC v3.0 Share-Alike You are welcome to use this library for commercial purposes.
